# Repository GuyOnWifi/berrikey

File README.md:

<h1 align="center">BerriKey</h1>

**A strawberry-themed, hardware key backed by a tamper-proof Secure Element. Built on top of the FIDO2 protocol. Simply plug it in to any site or app that supports the protocol and register a secure authenticator**

## Features

- **nRF52840** microcontroller
- **SE050**, EAL 6+ certified, tamper proof secure element storage for key storage and cryptography
- **USB-C and USB-A** connectivity
- **Capacitive touch pad** for user verification
- **Strawberry shaped case**

## Why?

I wanted to make an actually secure, open source hardware key that I could use for my accounts. Current options like [Yubikeys](https://www.yubico.com/products/) were great but not open-sourced, and community projects like [PicoKey](https://www.picokeys.com/) did not use tamper-resistant storages, and relied on a [chip with known vulnerabilites to it's security features](https://www.raspberrypi.com/news/security-through-transparency-rp2350-hacking-challenge-results-are-in/). I wanted to make it uniquely mine, so I made it strawberry themed!

### Threat model

The purpose of the project was to create a secure key to protected online identity (avoiding use of passwords, which can be keylogged, over-the-shoulder'ed, or leaked)

The main goals were to address the following:

- adversaries: should defend against well funded actors with lab equipment and knowledge (not state actors with supreme funding), evil maid attacks (semi-brief physical attacks)
- attack surface: all crypto operations are performed on SE, only USB (no nfc / ble).
- trust boundaries: SE is ultimate crypto trust, with all operations on the chip. firmware is trusted out of necessity

Most importantly, keys should never be cloneable off device, which would lead to compromise of online identity without knowledge. This mitigates the biggest risk of stealing the key, where the user is expected to assume that it is lost forever and immediately revoke the keys.

## Credits

Credit goes to the [Nitrokey Team](https://github.com/Nitrokey/nitrokey-3-firmware) for creating open-source keys, which this firmware is based on. Rather then reinviting a FIDO2 stack, I forked it off the battle-tested Nitrokey3 that has undergone security audits - ensuring its security against my threat model. It has been modified to support both a USB-C and USB-A, add support to custom LEDs, capacitive touch pads and easier support for programming with the nRF52840 chip. GHowever, the hardware is custom, with a unique form factor.

## Design

### Wiring

### PCB

### Case

## Building & Running

5 SWD pads have been exposed on the PCB. Wire them to a CMSIS-DAP debugger (I tested using the RPI debuprobe). Go into `firmware/utils/nrf-builder` and run `make full-deploy`. This will flash the bootloader, provision the keys and certificates, and then flash the firmware.

## Zine

Check it out [here](./zine.pdf)!

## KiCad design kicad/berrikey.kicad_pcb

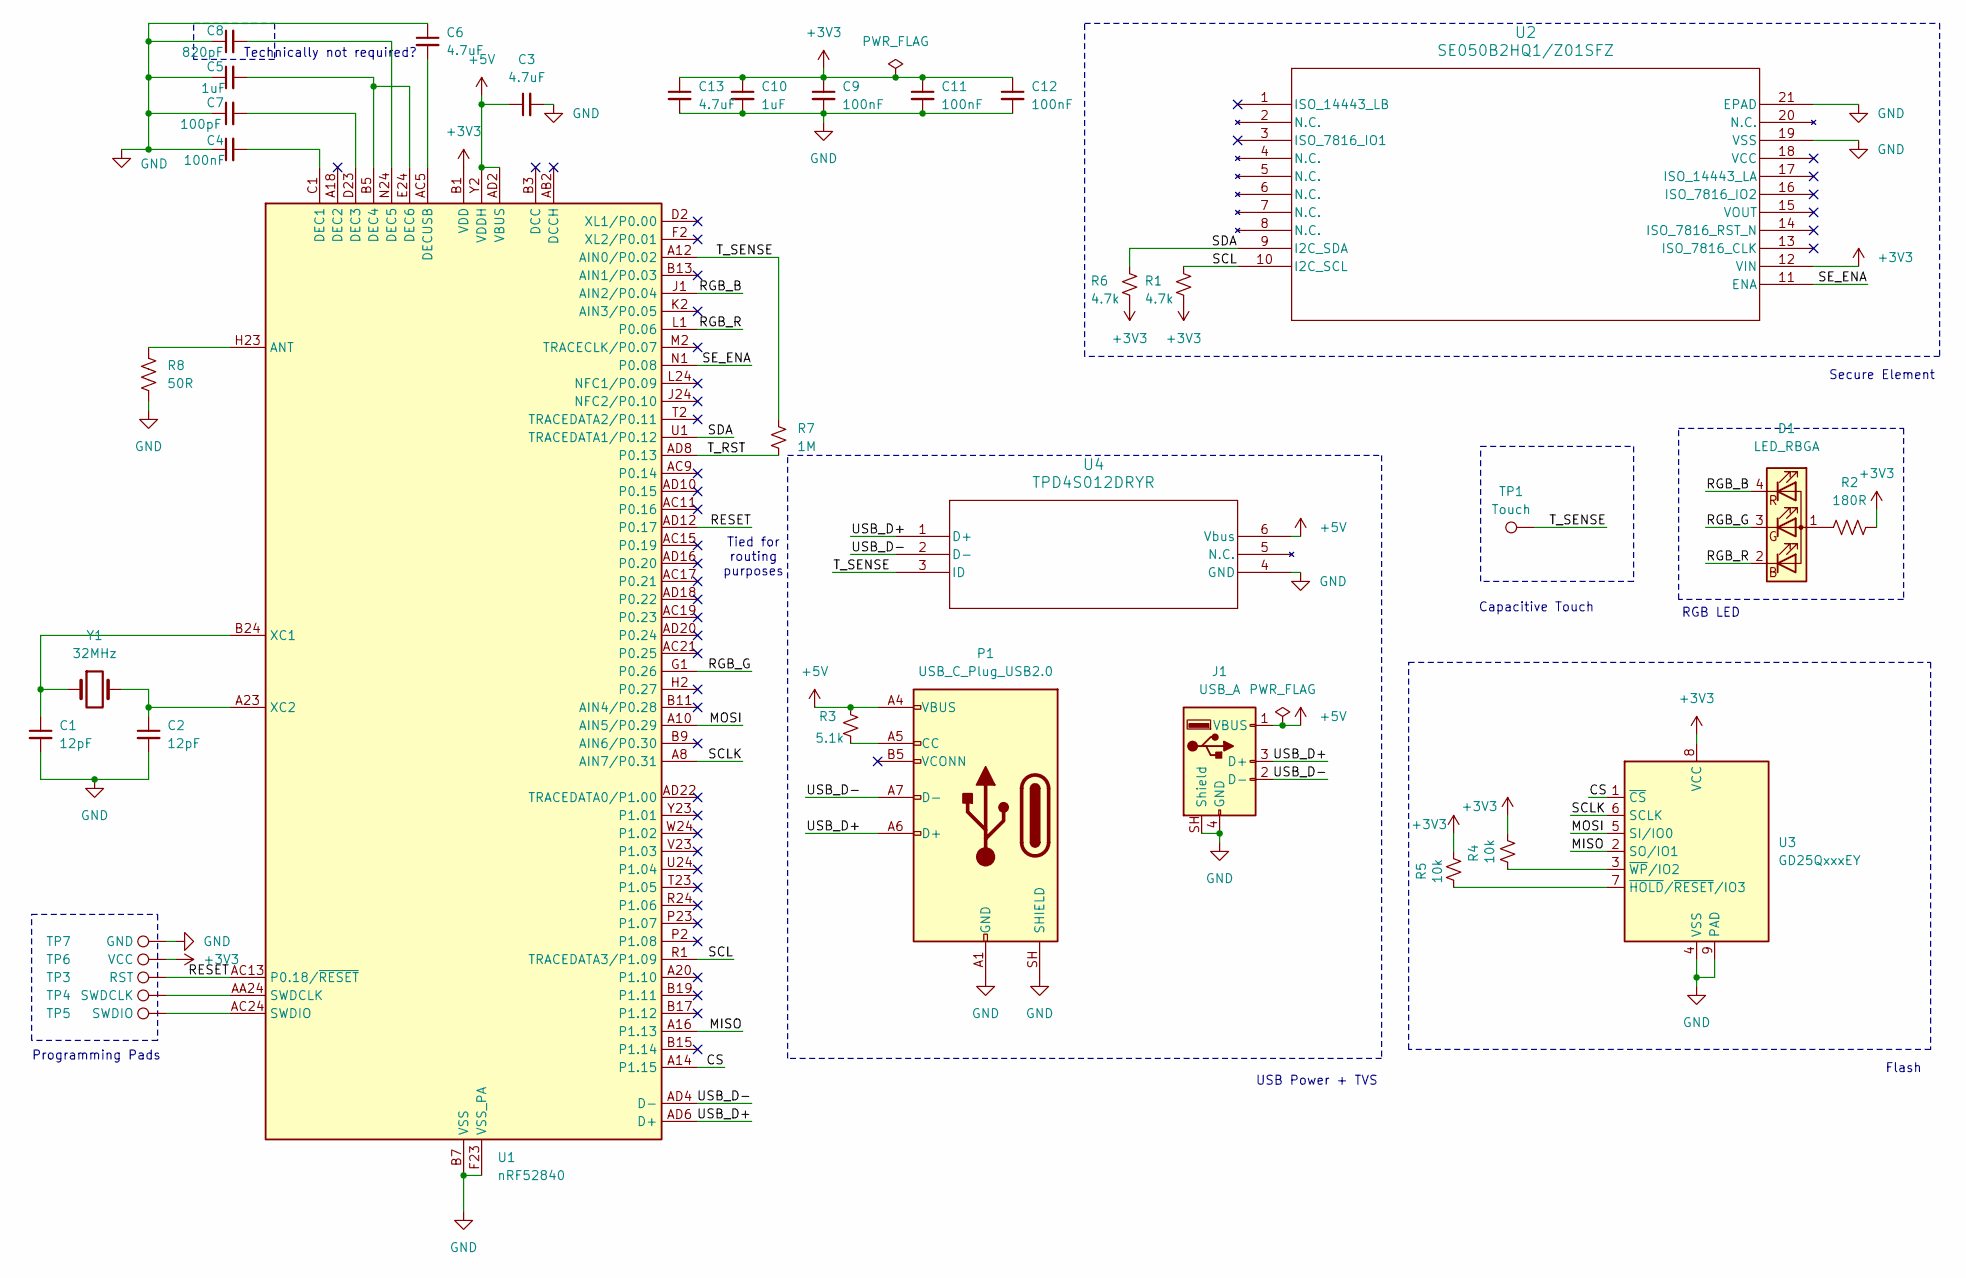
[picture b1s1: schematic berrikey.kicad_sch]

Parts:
C1, C2: 12pF; C_0603_1608Metric
C3, C6, C13: 4.7uF; C_0603_1608Metric
C4, C9, C11, C12: 100nF; C_0603_1608Metric
C5, C10: 1uF; C_0603_1608Metric
C7: 100pF; C_0603_1608Metric
C8: 820pF; C_0603_1608Metric
D1: LED_RBGA; LED_RGB_1210
J1: USB_A; USB_A_Molex_48037-2200_Horizontal
P1: USB_C_Plug_USB2.0; GCT_USB4155-03-C_REVA
R1, R6: 4.7k; R_0603_1608Metric
R2: 180R; R_0603_1608Metric
R3: 5.1k; R_0603_1608Metric
R4, R5: 10k; R_0603_1608Metric
R7: 1M; R_0603_1608Metric
R8: 50R; R_0603_1608Metric
TP1: Touch; Strawberry_Cap_Touch
TP3: RST; TestPoint_Pad_D2.0mm
TP4: SWDCLK; TestPoint_Pad_D2.0mm
TP5: SWDIO; TestPoint_Pad_D2.0mm
TP6: VCC; TestPoint_Pad_D2.0mm
TP7: GND; TestPoint_Pad_D2.0mm
U1: nRF52840; Nordic_AQFN-73-1EP_7x7mm_P0.5mm
U2: SE050B2HQ1/Z01SFZ; QFN20_SE050_NXP
U3: GD25QxxxEY; WSON-8-1EP_8x6mm_P1.27mm_EP3.4x4.3mm
U4: TPD4S012DRYR; DRY6
Y1: 32MHz; Crystal_SMD_2016-4Pin_2.0x1.6mm

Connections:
+3V3: C9.1, C10.1, C11.1, C12.1, C13.1, R1.2, R2.2, R4.1, R5.1, R6.2, TP6.1 (1_1), U1.A22 (VDD), U1.AD14 (VDD), U1.AD23 (VDD), U1.B1 (VDD), U1.W1 (VDD), U2.12 (VIN), U3.8 (VCC)
+5V: C3.1, J1.1 (VBUS), P1.A4 (VBUS), P1.A9 (VBUS), P1.B4 (VBUS), P1.B9 (VBUS), R3.1, U1.AD2 (VBUS), U1.Y2 (VDDH), U4.6 (Vbus)
/CS: U1.A14 (P1.15), U3.1 (~CS)
/MISO: U1.A16 (P1.13), U3.2 (SO/IO1)
/MOSI: U1.A10 (AIN5/P0.29), U3.5 (SI/IO0)
/RESET: TP3.1 (1_1), U1.AC13 (P0.18/~RESET), U1.AD12 (P0.17)
/RGB_B: D1.4 (RK), U1.J1 (AIN2/P0.04)
/RGB_G: D1.3 (GK), U1.G1 (P0.26)
/RGB_R: D1.2 (BK), U1.L1 (P0.06)
/SCL: R1.1, U1.R1 (TRACEDATA3/P1.09), U2.10 (I2C_SCL)
/SCLK: U1.A8 (AIN7/P0.31), U3.6 (SCLK)
/SDA: R6.1, U1.U1 (TRACEDATA1/P0.12), U2.9 (I2C_SDA)
/SE_ENA: U1.N1 (P0.08), U2.11 (ENA)
/T_RST: R7.2, U1.AD8 (P0.13)
/T_SENSE: R7.1, TP1.1 (1_1), U1.A12 (AIN0/P0.02), U4.3 (ID)
/USB_D+: J1.3 (D+), P1.A6 (D+), U1.AD6 (D+), U4.1 (D+)
/USB_D-: J1.2 (D-), P1.A7 (D-), U1.AD4 (D-), U4.2 (D-)
GND: C1.2, C2.2, C3.2, C4.1, C5.1, C6.1, C7.1, C8.1, C9.2, C10.2, C11.2, C12.2, C13.2, J1.4 (GND), J1.SH (Shield), P1.A1 (GND), P1.A12 (GND), P1.B1 (GND), P1.B12 (GND), P1.S1, P1.S2, P1.SH (SHIELD), R8.2, TP7.1 (1_1), U1.B7 (VSS), U1.EP (VSS), U1.F23 (VSS_PA), U2.19 (VSS), U2.21 (EPAD), U3.4 (VSS), U3.9 (PAD), U4.4 (GND), Y1.2, Y1.4
unnamed: D1.1 (A), R2.1
unnamed: P1.A5 (CC), R3.2
unnamed: R8.1, U1.H23 (ANT)
unnamed: C4.2, U1.C1 (DEC1)
unnamed: C7.2, U1.D23 (DEC3)
unnamed: C5.2, U1.B5 (DEC4), U1.E24 (DEC6)
unnamed: C8.2, U1.N24 (DEC5)
unnamed: C6.2, U1.AC5 (DECUSB)
unnamed: TP4.1 (1_1), U1.AA24 (SWDCLK)
unnamed: TP5.1 (1_1), U1.AC24 (SWDIO)
unnamed: C1.1, U1.B24 (XC1), Y1.1
unnamed: C2.1, U1.A23 (XC2), Y1.3
unnamed: R5.2, U3.7 (~HOLD/~RESET/IO3)
unnamed: R4.2, U3.3 (~WP/IO2)

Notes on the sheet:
RGB LED
Flash
Programming Pads
USB Power + TVS
Tied for routing purposes
Secure Element
Technically not required?
Capacitive Touch

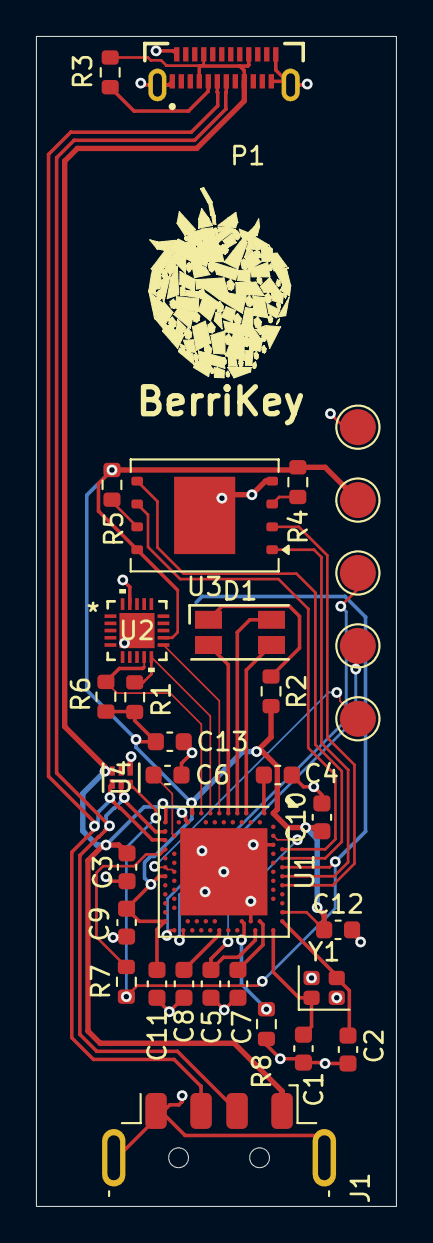
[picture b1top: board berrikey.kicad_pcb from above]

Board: 2 copper layers, 20.0 x 65.0 mm, 35 parts (1 on the bottom side), 32 nets.

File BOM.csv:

Id,Designator,Footprint,Quantity,Designation,JLCPCB ,JLCPCB Link,Price (JLC),"Digikey Links (unused for JLCPCB assembly, but in case you wanted to build yourself)"
1,"C1, C2",C_0603_1608Metric,2,12pF,Basic Auto Match,N/A,$0.01,https://www.digikey.ca/en/products/detail/yageo/CC0603JRNPO9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
2,"C3, C6, C13",C_0603_1608Metric,3,4.7uF,Basic Auto Match,N/A,$0.01,https://www.digikey.ca/en/products/detail/yageo/CC0603KRX5R7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
3,"C4, C9, C11, C12",C_0603_1608Metric,4,100nF,Basic Auto Match,N/A,$0.01,https://www.digikey.ca/en/products/detail/yageo/CC0603KRX7R9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
4,"C5, C10",C_0603_1608Metric,2,1uF,Basic Auto Match,N/A,$0.01,https://www.digikey.ca/en/products/detail/yageo/CC0603KRX5R9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
5,C7,C_0603_1608Metric,1,100pF,Basic Auto Match,N/A,$0.01,https://www.digikey.ca/en/products/detail/yageo/CC0603JRNPO9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
6,C8,C_0603_1608Metric,1,820pF,Basic Auto Match,N/A,$0.01,https://www.digikey.ca/en/products/detail/yageo/CC0603JRNPO9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
7,D1,LED_RGB_1210,1,LED_KRGB,FM-B2020RGBA-HG,https://jlcpcb.com/partdetail/110013-FM_B2020RGBAHG/C108793,$0.02,https://www.lcsc.com/product-detail/C108793.html
8,J1,USB_A_Molex_48037-2200_Horizontal,1,USB_A,48037-2200,https://jlcpcb.com/partdetail/MOLEX-480372200/C2765195,$1.01,https://www.digikey.ca/en/products/detail/molex/0480372200/2421361
9,P1,GCT_USB4155-03-C_REVA,1,USB_C_Plug_USB2.0,USB4155-03-C,https://jlcpcb.com/partdetail/5847867-USB4155_03C/C5183853,$2.22,https://www.digikey.ca/en/products/detail/gct/USB4155-03-C/14305161
10,"R1, R6",R_0603_1608Metric,2,4.7k,Basic Auto Match,N/A,$0.01,https://www.digikey.ca/en/products/detail/yageo/RC0603FR-074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
11,R2,R_0603_1608Metric,1,180R,Basic Auto Match,N/A,$0.01,https://www.digikey.ca/en/products/detail/yageo/RC0603FR-071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
12,R3,R_0603_1608Metric,1,5.1k,Basic Auto Match,N/A,$0.01,https://www.digikey.ca/en/products/detail/yageo/RC0603FR-075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
13,"R4, R5",R_0603_1608Metric,2,10k,Basic Auto Match,N/A,$0.01,https://www.digikey.ca/en/products/detail/yageo/RC0603FR-071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
14,R7,R_0603_1608Metric,1,1M,Basic Auto Match,N/A,$0.01,https://www.digikey.ca/en/products/detail/yageo/RC0603FR-071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
15,R8,R_0603_1608Metric,1,50R,Basic Auto Match,N/A,$0.01,https://www.digikey.ca/en/products/detail/yageo/RC0603FR-074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
16,TP1,Strawberry_Cap_Touch,1,Touch,N/A,N/A,N/A,N/A
17,TP3,TestPoint_Pad_D2.0mm,1,RST,N/A,N/A,N/A,N/A
18,TP4,TestPoint_Pad_D2.0mm,1,SWDCLK,N/A,N/A,N/A,N/A
19,TP5,TestPoint_Pad_D2.0mm,1,SWDIO,N/A,N/A,N/A,N/A
20,TP6,TestPoint_Pad_D2.0mm,1,VCC,N/A,N/A,N/A,N/A
21,TP7,TestPoint_Pad_D2.0mm,1,GND,N/A,N/A,N/A,N/A
22,U1,Nordic_AQFN-73-1EP_7x7mm_P0.5mm,1,nRF52840,NRF52840-QIAA-R,https://jlcpcb.com/partdetail/NordicSemicon-NRF52840_QIAAR/C190794,$5.73,https://www.digikey.ca/en/products/detail/nordic-semiconduct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
23,U2,QFN20_SE050_NXP,1,SE050B2HQ1/Z01SFZ,SE050C1HQ1/Z01SCZ,https://jlcpcb.com/partdetail/NXPSemicon-SE050C1HQ1Z01SCZ/C2650415,$6.17,https://www.digikey.ca/en/products/detail/nxp-usa-inc/SE050C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
24,U3,WSON-8-1EP_8x6mm_P1.27mm_EP3.4x4.3mm,1,GD25QxxxEY,GD25Q16CSIGR,https://jlcpcb.com/partdetail/376201-GD25Q16CSIGR/C395505,$1.09,https://www.digikey.ca/en/products/detail/gigadevice-semicon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
25,U4,DRY6,1,TPD4S012DRYR,TPD4S012DRYR,https://jlcpcb.com/partdetail/TexasInstruments-TPD4S012DRYR/C96506,$0.43,https://www.digikey.ca/en/products/detail/texas-instruments/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
26,Y1,Crystal_SMD_3225-4Pin_3.2x2.5mm,1,32MHz,Q22FA12800025,https://jlcpcb.com/partdetail/SeikoEpson-Q22FA12800025/C187794,$0.23,https://www.digikey.ca/en/products/detail/txc-corporation/7V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
Total,,,,,,,$17.02,

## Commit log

2026-06-20 WHOOO PROJECT
2026-06-20 add pricing
2026-06-22 Add 3d models, update README and pin mappings!
2026-06-22 updated 3d models!
2026-06-22 new model
2026-06-22 update readme!
2026-06-24 add magnets to BOM
